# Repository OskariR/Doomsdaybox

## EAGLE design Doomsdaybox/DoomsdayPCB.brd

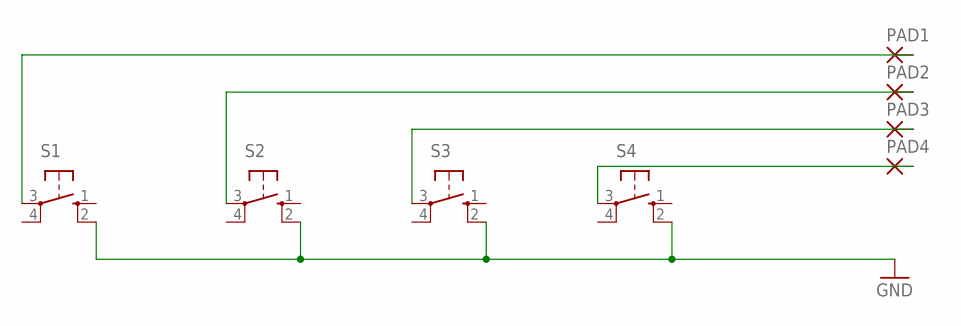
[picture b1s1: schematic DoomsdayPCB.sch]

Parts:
PAD1, PAD2, PAD3, PAD4: 2,54/1,0
S1, S2, S3, S4: 40-XX; B3F-40XX

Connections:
GND: S1.2 (S1), S2.2 (S1), S3.2 (S1), S4.2 (S1)
unnamed: PAD2.1, S2.3
unnamed: PAD1.1, S1.3
unnamed: PAD3.1, S3.3
unnamed: PAD4.1, S4.3

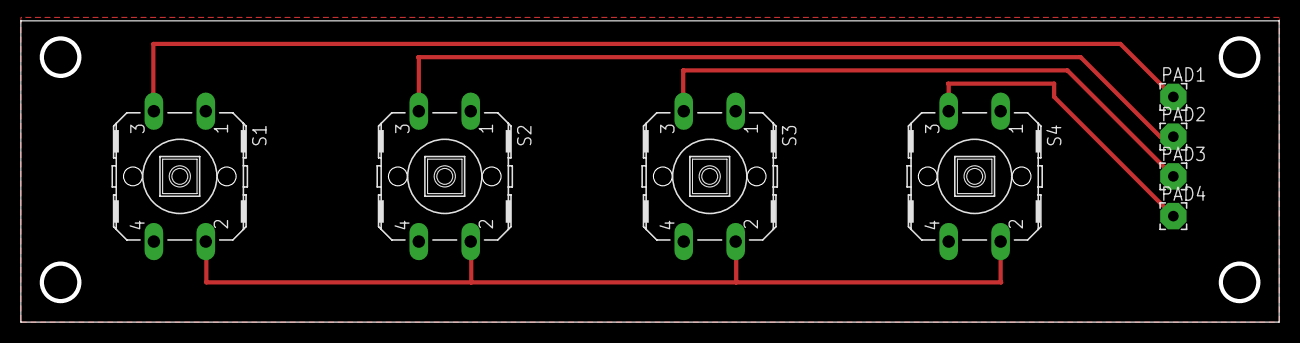
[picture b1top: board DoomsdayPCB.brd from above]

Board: 2 copper layers, 120.2 x 28.5 mm, 8 parts (0 on the bottom side), 5 nets.
